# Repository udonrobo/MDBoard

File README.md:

# MDBoard

## Overview
モタド制御用基板

## Description
・緑モタド，新緑モタド，谷川さんモタドを制御する基板<br>
・Eagleで作成

## Author
Rui Watanabe

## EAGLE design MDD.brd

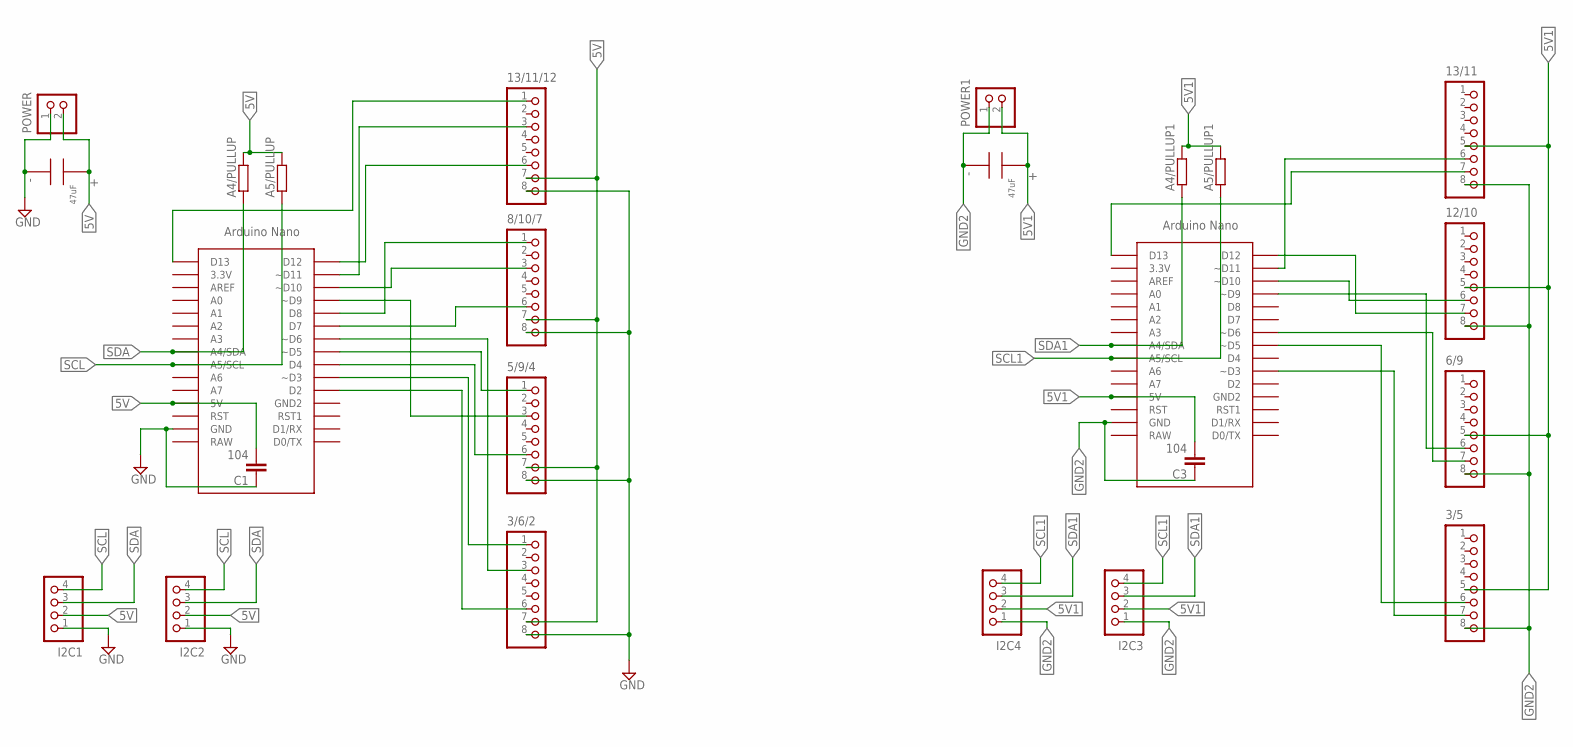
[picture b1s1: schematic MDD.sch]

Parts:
3/5, 3/6/2, 5/9/4, 6/9, 8/10/7, 12/10, 13/11, 13/11/12: B8B-XH-A
A4/PULLUP, A4/PULLUP1, A5/PULLUP, A5/PULLUP1: R-EU_0204/7; 0204/7
C1, C3: 104; C2.5-2
C2, C4: 47uF; C_47UF
I2C1, I2C2, I2C3, I2C4: B4B-XH-A
NANO, NANO1: NANO
POWER, POWER1: B2B-XH-A

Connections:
5V: 3/6/2.7, 5/9/4.7, 8/10/7.7, 13/11/12.7, A4/PULLUP.2, A5/PULLUP.2, C1.2, C2.+, I2C1.2, I2C2.2, NANO.5V, POWER.2 (VCC)
5V1: 3/5.5, 6/9.5, 12/10.5, 13/11.5, A4/PULLUP1.2, A5/PULLUP1.2, C3.2, C4.+, I2C3.2, I2C4.2, NANO1.5V, POWER1.2 (VCC)
GND: 3/6/2.8, 5/9/4.8, 8/10/7.8, 13/11/12.8, C1.1, C2.-, I2C1.1, I2C2.1, NANO.GND, POWER.1 (GND)
GND2: 3/5.8, 6/9.8, 12/10.8, 13/11.8, C3.1, C4.-, I2C3.1, I2C4.1, NANO1.GND, POWER1.1 (GND)
unnamed: 13/11/12.1, NANO.D13
unnamed: 13/11/12.3, NANO.D11 (~D11)
unnamed: 13/11/12.6, NANO.D12
unnamed: 8/10/7.3, NANO.D10 (~D10)
unnamed: 8/10/7.1, NANO.D8
unnamed: 5/9/4.3, NANO.D9 (~D9)
unnamed: 8/10/7.6, NANO.D7
unnamed: 3/6/2.3, NANO.D6 (~D6)
unnamed: 5/9/4.1, NANO.D5 (~D5)
unnamed: 5/9/4.6, NANO.D4
unnamed: 3/6/2.1, NANO.D3 (~D3)
unnamed: 3/6/2.6, NANO.D2
unnamed: 13/11.7, NANO1.D13
unnamed: 6/9.7, NANO1.D6 (~D6)
unnamed: 3/5.7, NANO1.D3 (~D3)
unnamed: 3/5.6, NANO1.D5 (~D5)
unnamed: 6/9.6, NANO1.D9 (~D9)
unnamed: 12/10.6, NANO1.D10 (~D10)
unnamed: 12/10.7, NANO1.D12
unnamed: 13/11.6, NANO1.D11 (~D11)
SCL: A5/PULLUP.1, I2C1.4, I2C2.4, NANO.A5 (A5/SCL)
SCL1: A5/PULLUP1.1, I2C3.4, I2C4.4, NANO1.A5 (A5/SCL)
SDA: A4/PULLUP.1, I2C1.3, I2C2.3, NANO.A4 (A4/SDA)
SDA1: A4/PULLUP1.1, I2C3.3, I2C4.3, NANO1.A4 (A4/SDA)

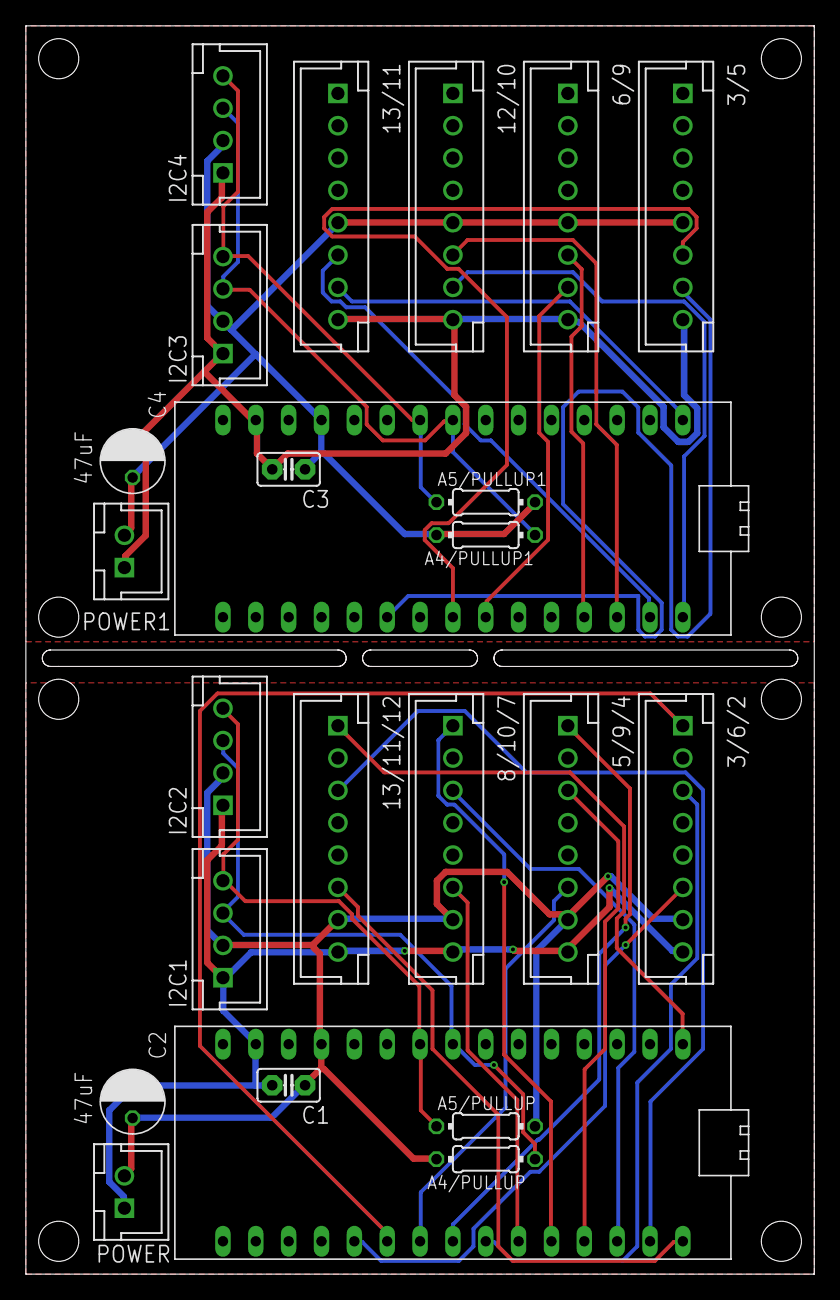
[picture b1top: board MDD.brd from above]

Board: 2 copper layers, 61.0 x 96.5 mm, 24 parts (0 on the bottom side), 28 nets.

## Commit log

2018-01-26 Create LICENCE
2018-01-26 add libraries
